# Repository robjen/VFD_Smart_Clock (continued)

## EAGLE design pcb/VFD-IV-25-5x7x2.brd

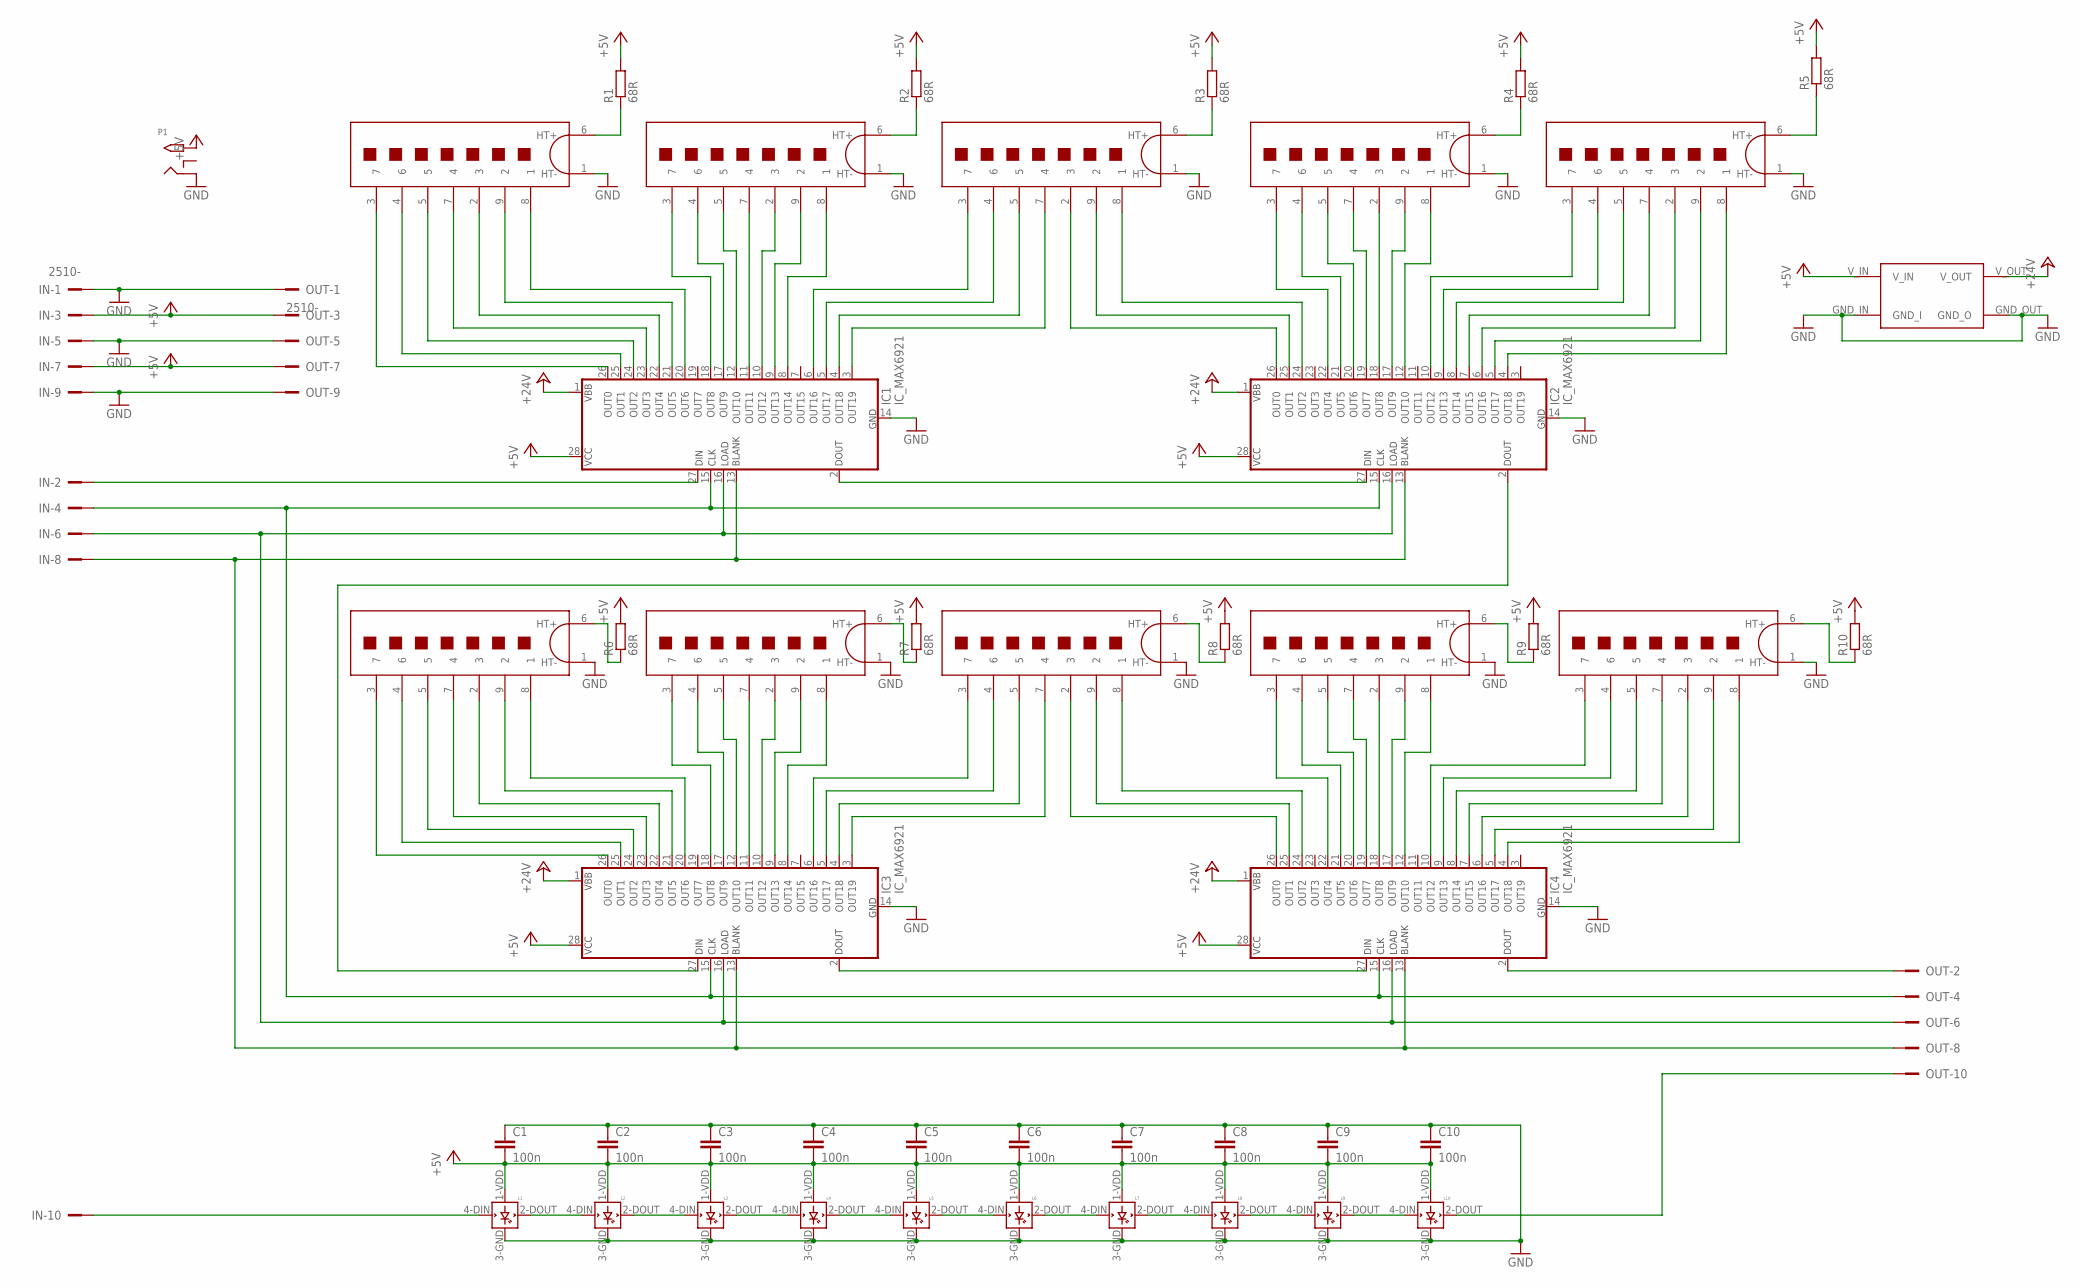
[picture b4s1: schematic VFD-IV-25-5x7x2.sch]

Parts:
1, 2, 3, 4, 5, 6, 7, 8, 9, 10: IV-25_DISP; IV-25
C1, C2, C3, C4, C5, C6, C7, C8, C9, C10: 100n; C050-025X075
IC1, IC2, IC3, IC4: IC_MAX6921; S28
IN: 2510-; PAK100/2500-10
L1, L2, L3, L4, L5, L6, L7, L8, L9, L10: WS2812B
OUT: 2510-; PAK100/2500-10
P1: 2.1MMJACKTHM; PJ-102A
R1, R2, R3, R4, R5, R6, R7, R8, R9, R10: 68R; 0207/10
U$11: STEP_UP_MODULE

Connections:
+5V: C1.2, C2.2, C3.2, C4.2, C5.2, C6.2, C7.2, C8.2, C9.2, C10.2, IC1.28 (VCC), IC2.28 (VCC), IC3.28 (VCC), IC4.28 (VCC), IN.3, IN.7, L1.1-VDD (VDD), L2.1-VDD (VDD), L3.1-VDD (VDD), L4.1-VDD (VDD), L5.1-VDD (VDD), L6.1-VDD (VDD), L7.1-VDD (VDD), L8.1-VDD (VDD), L9.1-VDD (VDD), L10.1-VDD (VDD), OUT.3, OUT.7, P1.TIP, R1.2, R2.2, R3.2, R4.2, R5.2, R6.2, R7.2, R8.2, R9.2, R10.2, U$11.V_IN
+24V: IC1.1 (VBB), IC2.1 (VBB), IC3.1 (VBB), IC4.1 (VBB), U$11.V_OUT
GND: 1.1 (HT-), 2.1 (HT-), 3.1 (HT-), 4.1 (HT-), 5.1 (HT-), 6.1 (HT-), 7.1 (HT-), 8.1 (HT-), 9.1 (HT-), 10.1 (HT-), C1.1, C2.1, C3.1, C4.1, C5.1, C6.1, C7.1, C8.1, C9.1, C10.1, IC1.14 (GND), IC2.14 (GND), IC3.14 (GND), IC4.14 (GND), IN.1, IN.5, IN.9, L1.3-GND (GND), L2.3-GND (GND), L3.3-GND (GND), L4.3-GND (GND), L5.3-GND (GND), L6.3-GND (GND), L7.3-GND (GND), L8.3-GND (GND), L9.3-GND (GND), L10.3-GND (GND), OUT.1, OUT.5, OUT.9, P1.RING, U$11.GND_IN (GND_I), U$11.GND_OUT (GND_O)
unnamed: L1.2-DOUT (DOUT), L2.4-DIN (DIN)
unnamed: L2.2-DOUT (DOUT), L3.4-DIN (DIN)
unnamed: L3.2-DOUT (DOUT), L4.4-DIN (DIN)
unnamed: L4.2-DOUT (DOUT), L5.4-DIN (DIN)
unnamed: L5.2-DOUT (DOUT), L6.4-DIN (DIN)
unnamed: L6.2-DOUT (DOUT), L7.4-DIN (DIN)
unnamed: L7.2-DOUT (DOUT), L8.4-DIN (DIN)
unnamed: L8.2-DOUT (DOUT), L9.4-DIN (DIN)
unnamed: L9.2-DOUT (DOUT), L10.4-DIN (DIN)
unnamed: 1.3 (7), IC1.26 (OUT0)
unnamed: 1.4 (6), IC1.25 (OUT1)
unnamed: 1.5, IC1.24 (OUT2)
unnamed: 1.7 (4), IC1.23 (OUT3)
unnamed: 1.2 (3), IC1.22 (OUT4)
unnamed: 1.9 (2), IC1.21 (OUT5)
unnamed: 1.8 (1), IC1.20 (OUT6)
unnamed: 2.3 (7), IC1.18 (OUT8)
unnamed: 2.4 (6), IC1.17 (OUT9)
unnamed: 2.5, IC1.12 (OUT10)
unnamed: 2.7 (4), IC1.11 (OUT11)
unnamed: 2.2 (3), IC1.10 (OUT12)
unnamed: 2.9 (2), IC1.9 (OUT13)
unnamed: 2.8 (1), IC1.8 (OUT14)
unnamed: 3.3 (7), IC1.6 (OUT16)
unnamed: 3.4 (6), IC1.5 (OUT17)
unnamed: 4.3 (7), IC2.22 (OUT4)
unnamed: 4.4 (6), IC2.21 (OUT5)
unnamed: 3.5, IC1.4 (OUT18)
unnamed: 3.7 (4), IC1.3 (OUT19)
unnamed: 3.2 (3), IC2.26 (OUT0)
unnamed: 3.9 (2), IC2.25 (OUT1)
unnamed: 3.8 (1), IC2.24 (OUT2)
unnamed: 4.5, IC2.20 (OUT6)
unnamed: 4.7 (4), IC2.19 (OUT7)
unnamed: 4.2 (3), IC2.18 (OUT8)
unnamed: 4.9 (2), IC2.17 (OUT9)
unnamed: 4.8 (1), IC2.12 (OUT10)
unnamed: 5.3 (7), IC2.10 (OUT12)
unnamed: 5.4 (6), IC2.9 (OUT13)
unnamed: 5.5, IC2.8 (OUT14)
unnamed: 5.7 (4), IC2.7 (OUT15)
unnamed: 5.2 (3), IC2.6 (OUT16)
unnamed: 5.9 (2), IC2.5 (OUT17)
unnamed: 5.8 (1), IC2.4 (OUT18)
unnamed: 6.3 (7), IC3.26 (OUT0)
unnamed: 6.4 (6), IC3.25 (OUT1)
unnamed: 6.5, IC3.24 (OUT2)
unnamed: 6.7 (4), IC3.23 (OUT3)
unnamed: 6.2 (3), IC3.22 (OUT4)
unnamed: 6.9 (2), IC3.21 (OUT5)
unnamed: 6.8 (1), IC3.20 (OUT6)
unnamed: 7.3 (7), IC3.18 (OUT8)
unnamed: 7.4 (6), IC3.17 (OUT9)
unnamed: 7.5, IC3.12 (OUT10)
unnamed: 7.7 (4), IC3.11 (OUT11)
unnamed: 7.2 (3), IC3.10 (OUT12)
unnamed: 7.9 (2), IC3.9 (OUT13)
unnamed: 7.8 (1), IC3.8 (OUT14)
unnamed: 8.3 (7), IC3.6 (OUT16)
unnamed: 8.4 (6), IC3.5 (OUT17)
unnamed: 8.5, IC3.4 (OUT18)
unnamed: 8.7 (4), IC3.3 (OUT19)
unnamed: 8.2 (3), IC4.26 (OUT0)
unnamed: 8.9 (2), IC4.25 (OUT1)
unnamed: 8.8 (1), IC4.24 (OUT2)
unnamed: 9.3 (7), IC4.22 (OUT4)
unnamed: 9.4 (6), IC4.21 (OUT5)
unnamed: 9.5, IC4.20 (OUT6)
unnamed: 9.7 (4), IC4.19 (OUT7)
unnamed: 9.2 (3), IC4.18 (OUT8)
unnamed: 9.9 (2), IC4.17 (OUT9)
unnamed: 9.8 (1), IC4.12 (OUT10)
unnamed: 10.3 (7), IC4.10 (OUT12)
unnamed: 10.4 (6), IC4.9 (OUT13)
unnamed: 10.5, IC4.8 (OUT14)
unnamed: 10.7 (4), IC4.7 (OUT15)
unnamed: 10.2 (3), IC4.6 (OUT16)
unnamed: 10.9 (2), IC4.5 (OUT17)
unnamed: 10.8 (1), IC4.4 (OUT18)
unnamed: IC1.2 (DOUT), IC2.27 (DIN)
unnamed: IC2.2 (DOUT), IC3.27 (DIN)
unnamed: IC3.2 (DOUT), IC4.27 (DIN)
unnamed: IC1.27 (DIN), IN.2
unnamed: IN.10, L1.4-DIN (DIN)
unnamed: L10.2-DOUT (DOUT), OUT.10
unnamed: IC4.2 (DOUT), OUT.2
unnamed: IC1.15 (CLK), IC2.15 (CLK), IC3.15 (CLK), IC4.15 (CLK), IN.4, OUT.4
unnamed: IC1.16 (LOAD), IC2.16 (LOAD), IC3.16 (LOAD), IC4.16 (LOAD), IN.6, OUT.6
unnamed: 5.6 (HT+), R5.1
unnamed: IC1.13 (BLANK), IC2.13 (BLANK), IC3.13 (BLANK), IC4.13 (BLANK), IN.8, OUT.8
unnamed: 4.6 (HT+), R4.1
unnamed: 3.6 (HT+), R3.1
unnamed: 2.6 (HT+), R2.1
unnamed: 1.6 (HT+), R1.1
unnamed: 9.6 (HT+), R9.1
unnamed: 10.6 (HT+), R10.1
unnamed: 8.6 (HT+), R8.1
unnamed: 7.6 (HT+), R7.1
unnamed: 6.6 (HT+), R6.1

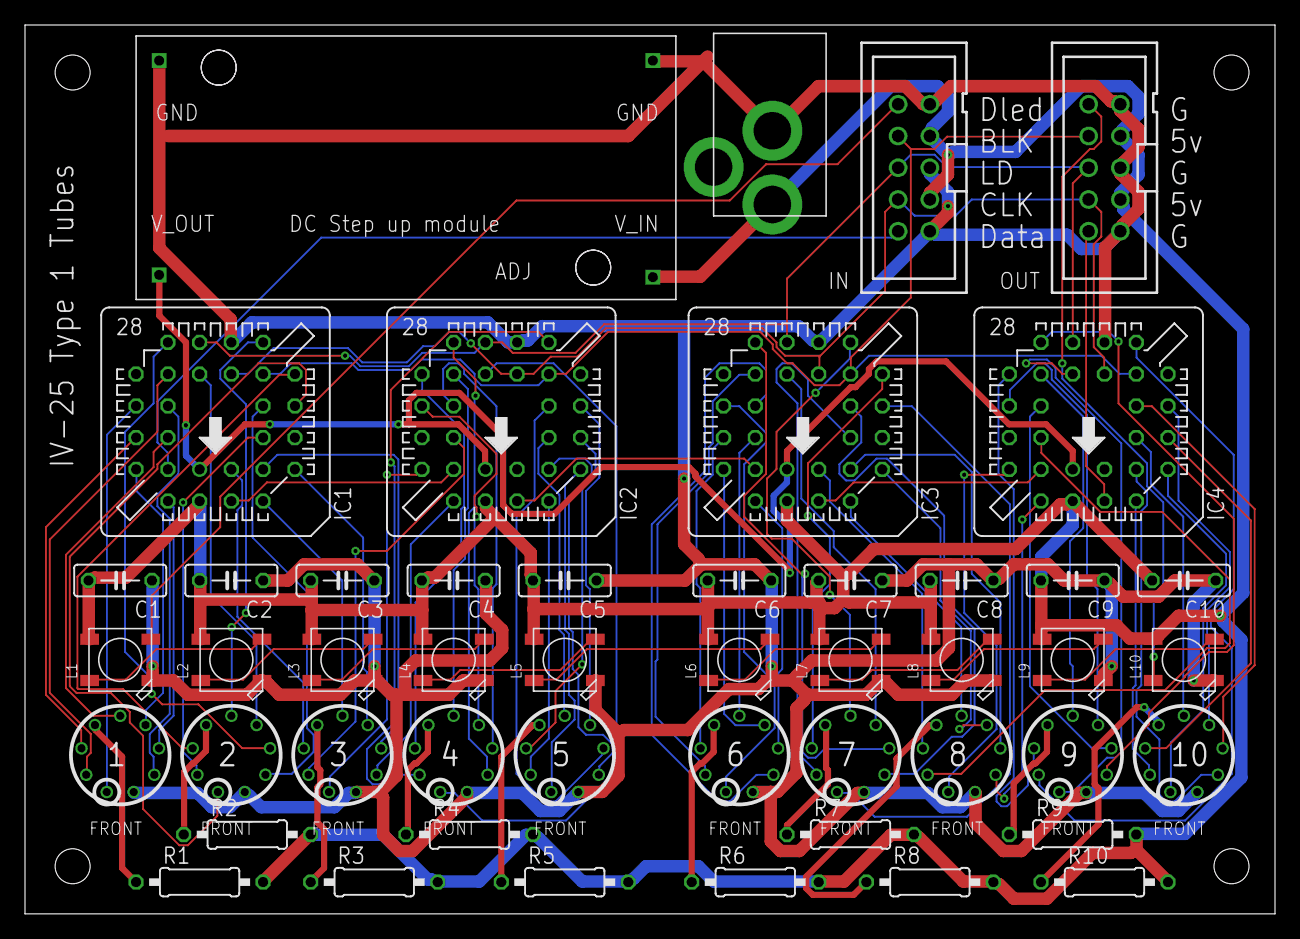
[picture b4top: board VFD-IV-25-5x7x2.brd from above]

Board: 2 copper layers, 100.0 x 71.1 mm, 48 parts (0 on the bottom side), 102 nets.

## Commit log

2017-05-16 flesh out the read me
2019-01-21 Add files via upload
    arduino file for wemos ticking clock ... example of how to use yield to keep things alive
